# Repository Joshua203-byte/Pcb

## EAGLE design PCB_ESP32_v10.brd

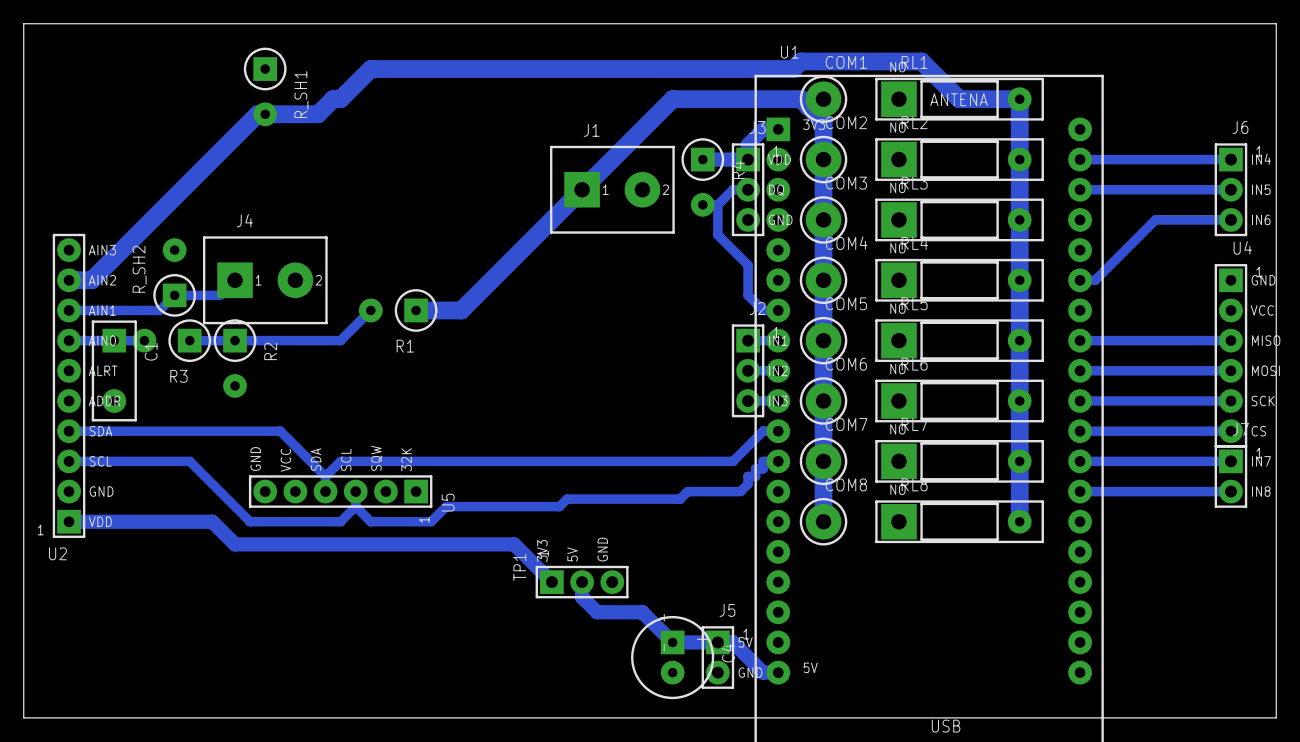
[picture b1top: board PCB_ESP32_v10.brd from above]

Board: 2 copper layers, 105.4 x 58.4 mm, 36 parts (0 on the bottom side), 23 nets.

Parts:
C1: 0.1u; CAP_5MM
C4: 10u 16V; CAP_E_2_54
COM1: COM K1; WIREPAD
COM2: COM K2; WIREPAD
COM3: COM K3; WIREPAD
COM4: COM K4; WIREPAD
COM5: COM K5; WIREPAD
COM6: COM K6; WIREPAD
COM7: COM K7; WIREPAD
COM8: COM K8; WIREPAD
J1: Panel; TERM2_5MM
J2: Reles IN1-IN3; MALE_1X03
J3: DS18B20; MALE_1X03
J4: Celda referencia; TERM2_5MM
J5: Rele 5V y GND; MALE_1X02
J6: Reles IN4-IN6; MALE_1X03
J7: Reles IN7-IN8; MALE_1X02
R1: 33k 1%; RES_V
R2: 10k 1%; RES_V
R3: 1k; RES_V
R4: 4.7k; RES_V
RL1: 2.2; RES_H_T
RL2: 4.7; RES_H_T
RL3: 10; RES_H_T
RL4: 22; RES_H_T
RL5: 47; RES_H_T
RL6: 100; RES_H_T
RL7: 220; RES_H_T
RL8: 470; RES_H_T
R_SH1, R_SH2: 1; RES_V
TP1: Puntos de prueba; MALE_1X03
U1: ESP32 DevKitC 38 pines; ESP32_DEVKIT38
U2: ADS1115 (modulo); SOCKET_1X10
U4: Modulo microSD SPI; SOCKET_1X06
U5: Modulo RTC DS3231; SOCKET_1X06

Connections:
3V3: J3.1, R4.1, TP1.1, U1.1, U2.1, U5.5
5V: C4.1, J5.1, TP1.2, U1.19, U4.2
A0: C1.1, R3.2, U2.7
CS: U1.28, U4.6
DIV: R1.2, R2.1, R3.1
DQ: J3.2, R4.2, U1.7
GND: C1.2, C4.2, J1.2, J3.3, J4.2, J5.2, R2.2, R_SH1.1, R_SH2.2, TP1.3, U1.14, U1.32, U2.2, U2.5, U2.10, U4.1, U5.6
IN1: J2.1, U1.8
IN2: J2.2, U1.9
IN3: J2.3, U1.10
IN4: J6.1, U1.37
IN5: J6.2, U1.36
IN6: J6.3, U1.33
IN7: J7.1, U1.27
IN8: J7.2, U1.26
LB: RL1.2, RL2.2, RL3.2, RL4.2, RL5.2, RL6.2, RL7.2, RL8.2, R_SH1.2, U2.9
MISO: U1.31, U4.3
MOSI: U1.30, U4.4
PV: COM1.1, COM2.1, COM3.1, COM4.1, COM5.1, COM6.1, COM7.1, COM8.1, J1.1, R1.1
REF: J4.1, R_SH2.1, U2.8
SCK: U1.29, U4.5
SCL: U1.12, U2.3, U5.3
SDA: U1.11, U2.4, U5.4
